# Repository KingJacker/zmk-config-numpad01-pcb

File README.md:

# NumPad01 - PCB

This Repository outlines the requirements to build a custom Keyboard with an expanded Numpad layout.

## Hardware
This Keyboard is built using the NiceNanoV2 NRF Module to leverage its Bluetooth capabilities.

It is possible to Handwire this keyboard. Altough it was deisgned with a PCB in mind.

The KiCAD files can be found in [Numpad1](/Numpad1/).
The PCB is designed to use MX Hotswap sockets.

### Key Layout
The expanded Numpad layout looks as follows.\

### Wiring
In the following Diagram it is described which pins of the NiceNanoV2 are to be soldered to the Pads on the PCB.

### Enclosure
I have deisgned a very slim Case for the PCB with just enough space for a small LiPo. You can find the OnShape Project at this [Link](https://cad.onshape.com/documents/f554f5fd452e23ddbeb69b48/w/c72bd622fd985e9e9cbd8d4f/e/263bace952513a244bd67565) or checkout the STEP files in [CAD/case](CAD/case).

###  Keycaps
This Keyboard has 21 Keys in Total.
| Amount | Type |
| ------ |----- |
| 18     | 1u   |
| 3      | 2u   |

Custom Keycaps were designed for this project, while 3D printed Keycaps may not be optimal they surely look good.

You can find the OnShape Project at this [Link](https://cad.onshape.com/documents/af3d93fce92099b4708cc048/w/839bc3040b2b1ff49a4ff1b0/e/539817a75a59442267b910fb). Since I made multiple versions I won't upload them here.

## Firmware
To utilize the full Bluetooth capabilites of the NiceNanoV2 the ZMK firmware was used. This the Keymap of this config can be changed using [Nick's Keymap Editor](https://nickcoutsos.github.io/keymap-editor/).

You can find the latest firmware on the [Releases](https://github.com/KingJacker/zmk-config-numpad01-pcb/releases/tag/release) Page.

### Flashing
If you are starting out and haven't falshed anything to the NiceNanoV2, you need to short the RESET pin to GND twice in short succession while plugged in via USB C. 

The red light will Blink and a drive will appear on your computer with the name "NiceNanoV2". Simply drag the firmware file into drive. 

That's it, the drive will disappear and the NiceNanoV2 will reboot.

Once you have flashed this firmware you can always access the bootloader to update the firmware by pressing the Layer 1 Key and Plus at the same time.

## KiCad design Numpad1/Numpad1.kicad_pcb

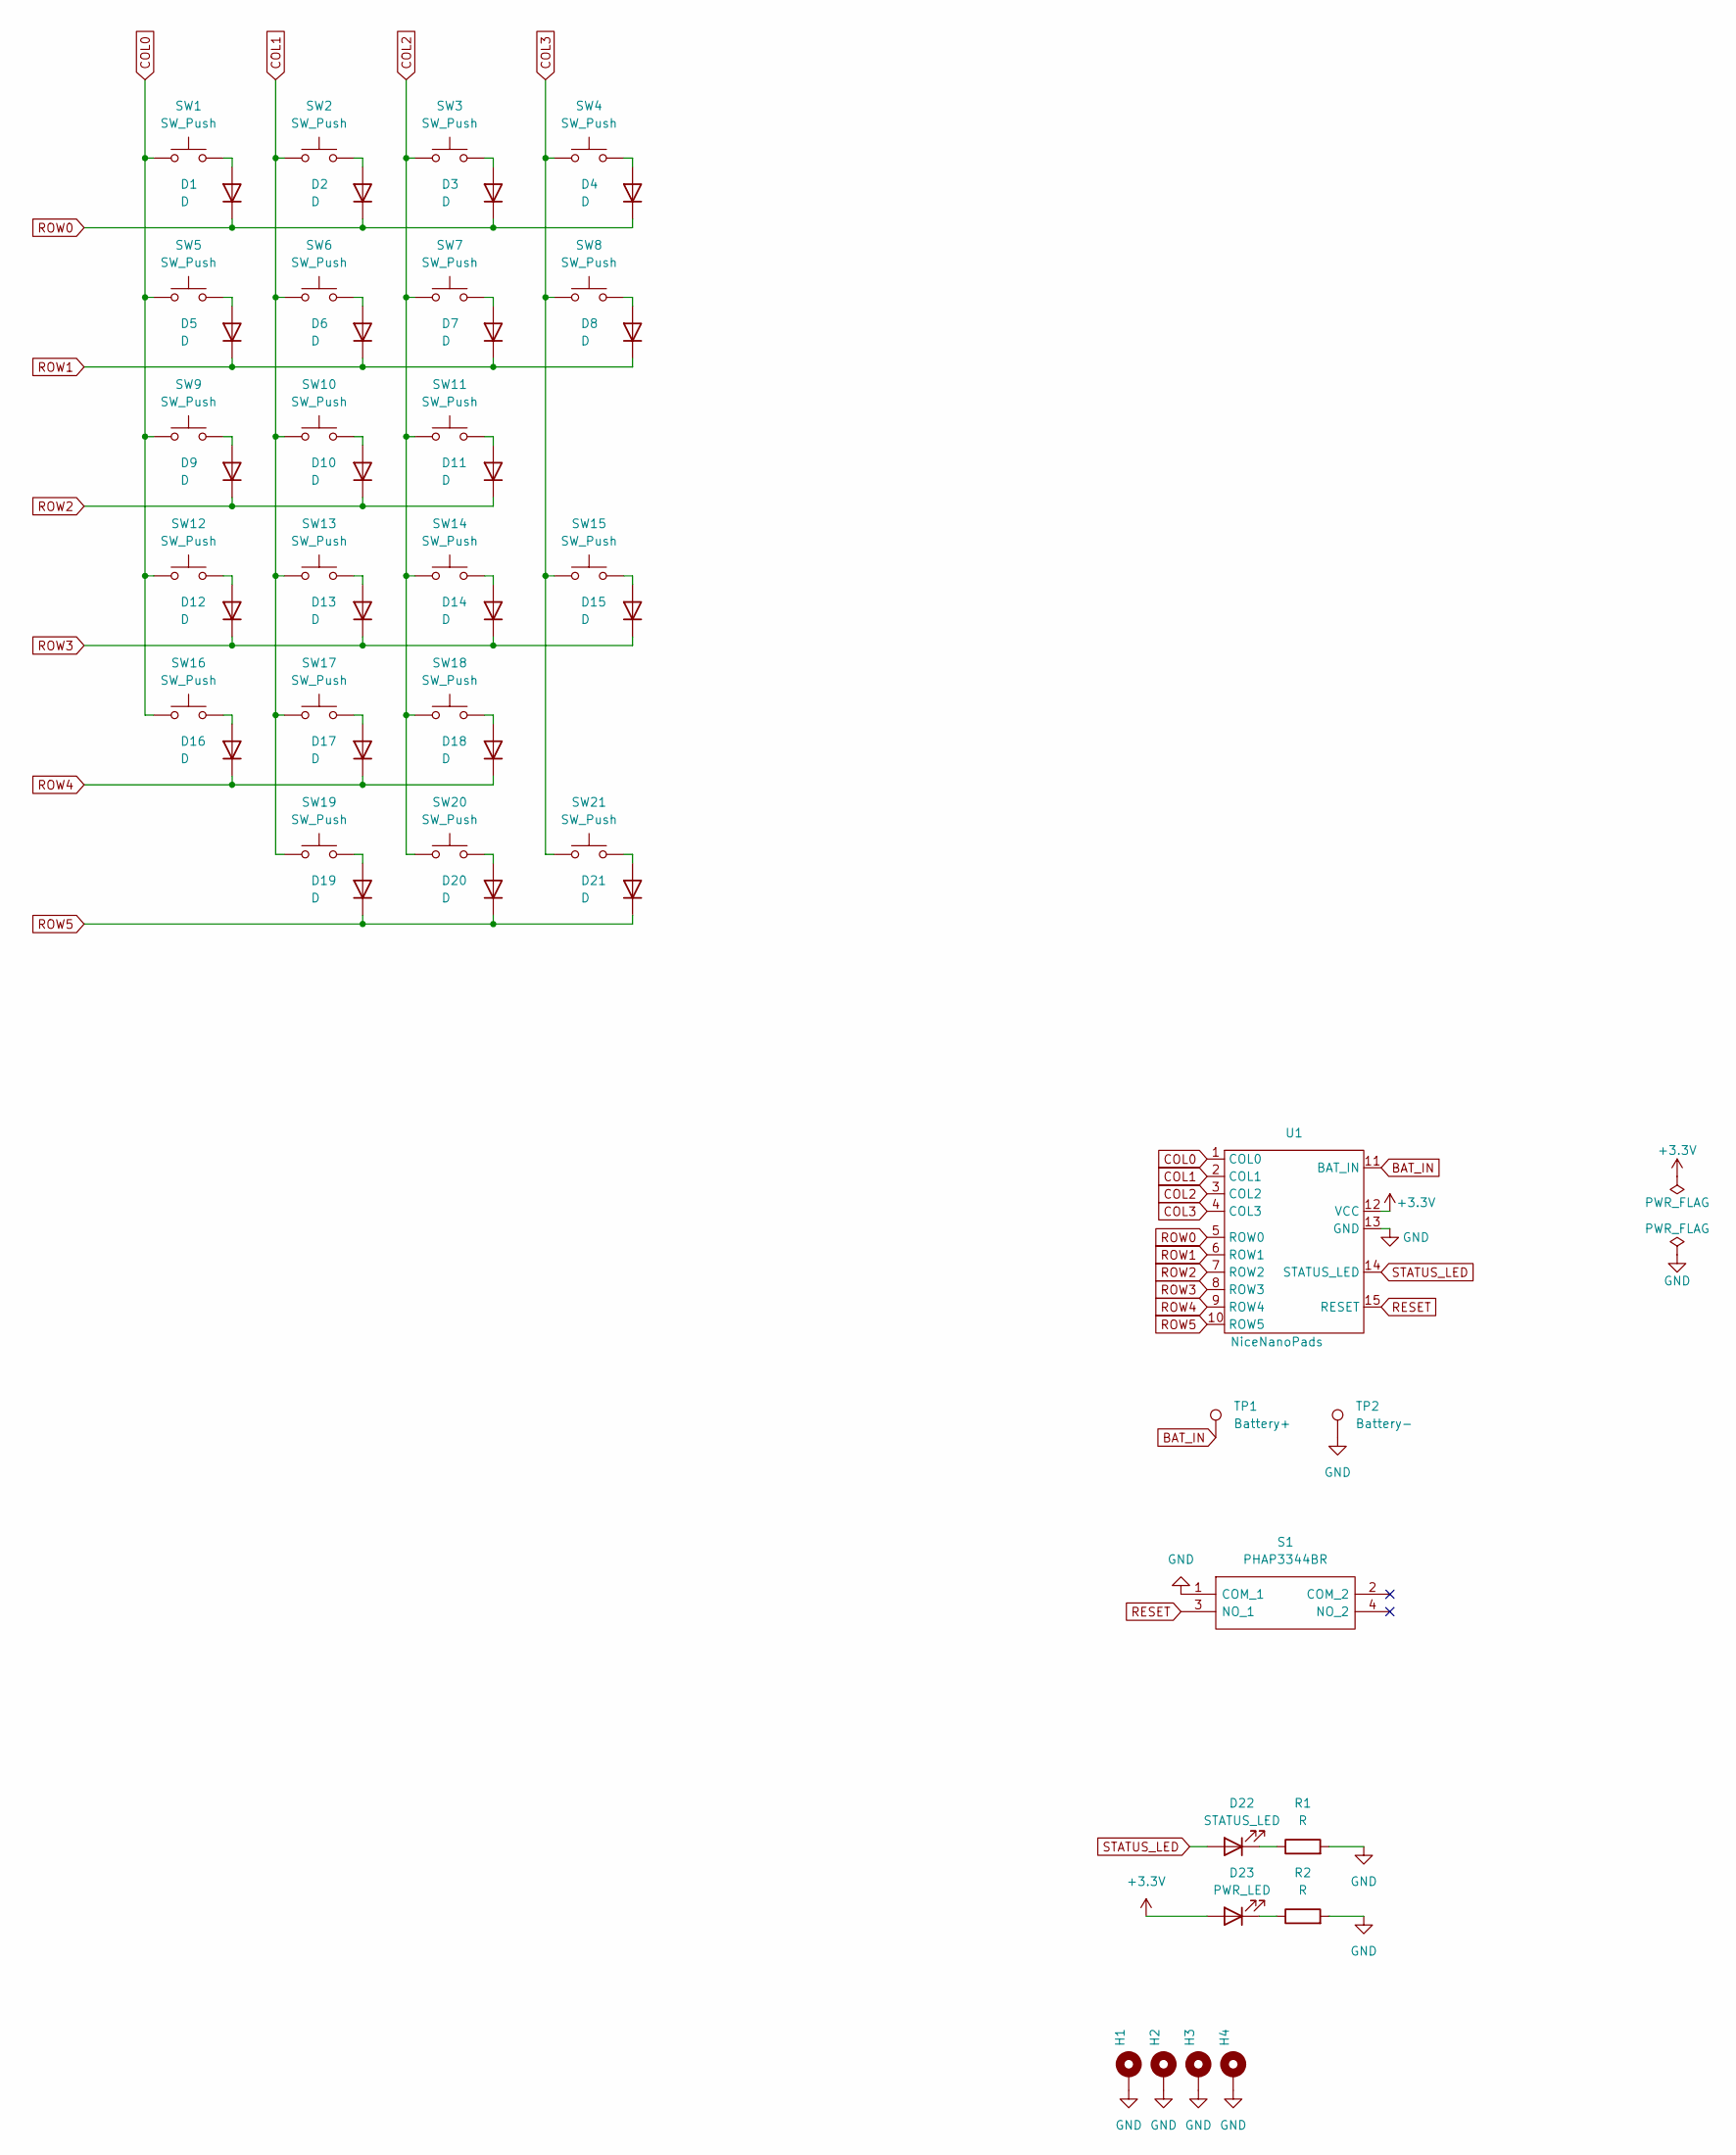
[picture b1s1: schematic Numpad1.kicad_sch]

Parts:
D1, D2, D3, D4, D5, D6, D7, D8, D9, D10, D11, D12, D13, D14, D15, D16, D17, D18, D19, D20, D21: D; D_SOD-123
D22: STATUS_LED; LED_0805_2012Metric_Pad1.15x1.40mm_HandSolder
D23: PWR_LED; LED_0805_2012Metric_Pad1.15x1.40mm_HandSolder
H1, H2, H3, H4: MountingHole_Pad; MountingHole_3.2mm_M3_DIN965_Pad
R1, R2: R; R_0805_2012Metric_Pad1.20x1.40mm_HandSolder
S1: PHAP3344BR; PTS526SM15SMTR2LFS; Mouser Part Number 642-PHAP3344BR
SW1, SW2, SW3, SW4, SW5, SW6, SW7, SW8, SW9, SW10, SW11, SW12, SW13, SW14, SW16, SW17, SW18, SW20: SW_Push; SW_Hotswap_Kailh_MX_1.00u
SW15, SW21: SW_Push; SW_Hotswap_Kailh_MX_2.00u_90deg
SW19: SW_Push; SW_Hotswap_Kailh_MX_2.00u
TP1: Battery+; TestPoint_Pad_D4.0mm
TP2: Battery-; TestPoint_Pad_D4.0mm
U1: NiceNanoPads

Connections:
+3.3V: D23.2 (A), U1.12 (VCC)
BAT_IN: TP1.1, U1.11 (BAT_IN); also elsewhere on the board
COL0: SW1.1, SW5.1, SW9.1, SW12.1, SW16.1, U1.1 (COL0)
COL1: SW2.1, SW6.1, SW10.1, SW13.1, SW17.1, SW19.1, U1.2 (COL1)
COL2: SW3.1, SW7.1, SW11.1, SW14.1, SW18.1, SW20.1, U1.3 (COL2)
COL3: SW4.1, SW8.1, SW15.1, SW21.1, U1.4 (COL3)
GND: H1.1, H2.1, H3.1, H4.1, R1.2, R2.2, S1.1 (COM_1), TP2.1, U1.13 (GND); also elsewhere on the board
unnamed: D1.2 (A), SW1.2
unnamed: D2.2 (A), SW2.2
unnamed: D3.2 (A), SW3.2
unnamed: D4.2 (A), SW4.2
unnamed: D5.2 (A), SW5.2
unnamed: D6.2 (A), SW6.2
unnamed: D7.2 (A), SW7.2
unnamed: D8.2 (A), SW8.2
unnamed: D9.2 (A), SW9.2
unnamed: D10.2 (A), SW10.2
unnamed: D11.2 (A), SW11.2
unnamed: D12.2 (A), SW12.2
unnamed: D13.2 (A), SW13.2
unnamed: D14.2 (A), SW14.2
unnamed: D15.2 (A), SW15.2
unnamed: D16.2 (A), SW16.2
unnamed: D17.2 (A), SW17.2
unnamed: D18.2 (A), SW18.2
unnamed: D19.2 (A), SW19.2
unnamed: D20.2 (A), SW20.2
unnamed: D21.2 (A), SW21.2
unnamed: D22.1 (K), R1.1
unnamed: D23.1 (K), R2.1
RESET: S1.3 (NO_1), U1.15 (RESET)
ROW0: D1.1 (K), D2.1 (K), D3.1 (K), D4.1 (K), U1.5 (ROW0)
ROW1: D5.1 (K), D6.1 (K), D7.1 (K), D8.1 (K), U1.6 (ROW1)
ROW2: D9.1 (K), D10.1 (K), D11.1 (K), U1.7 (ROW2)
ROW3: D12.1 (K), D13.1 (K), D14.1 (K), D15.1 (K), U1.8 (ROW3)
ROW4: D16.1 (K), D17.1 (K), D18.1 (K), U1.9 (ROW4)
ROW5: D19.1 (K), D20.1 (K), D21.1 (K), U1.10 (ROW5)
STATUS_LED: D22.2 (A), U1.14 (STATUS_LED)

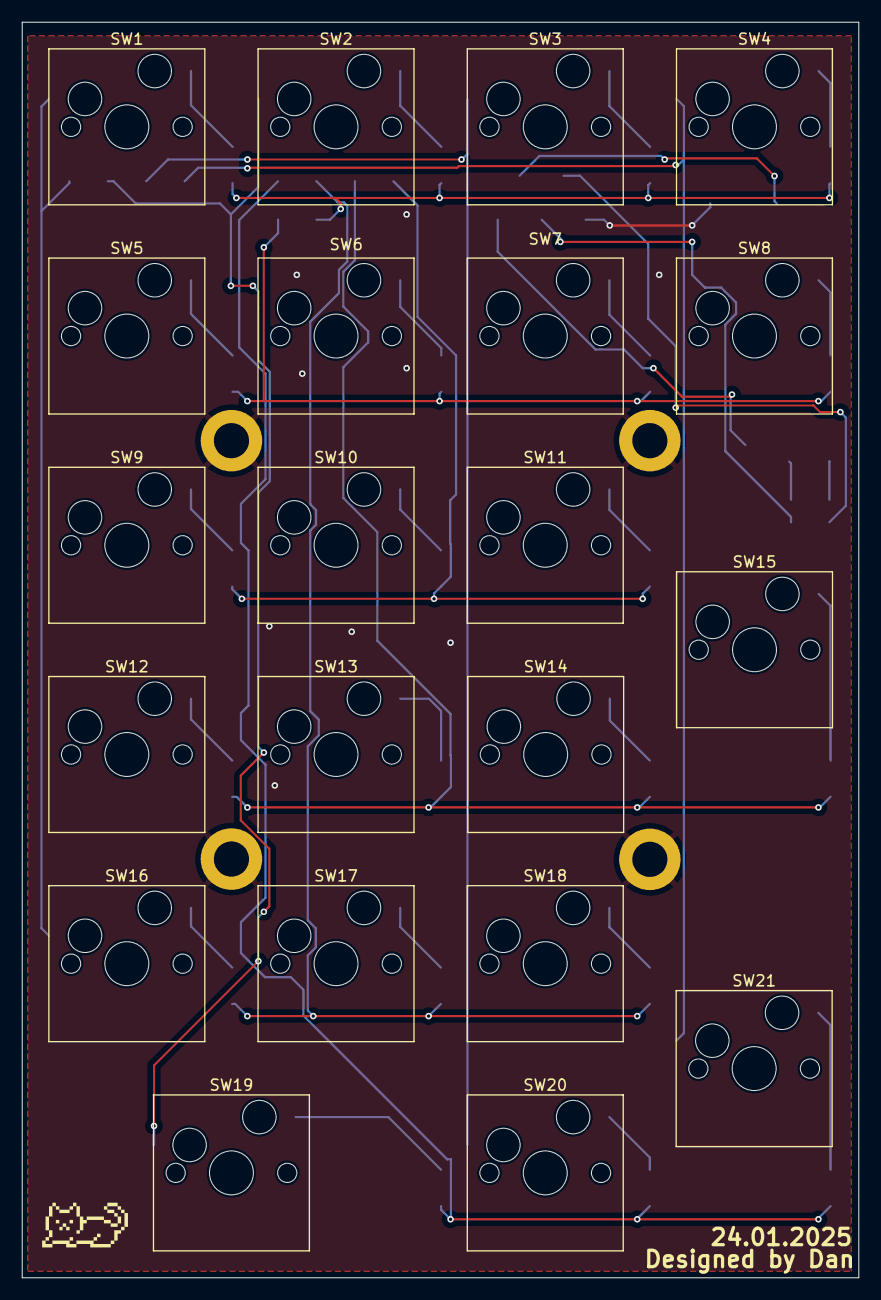
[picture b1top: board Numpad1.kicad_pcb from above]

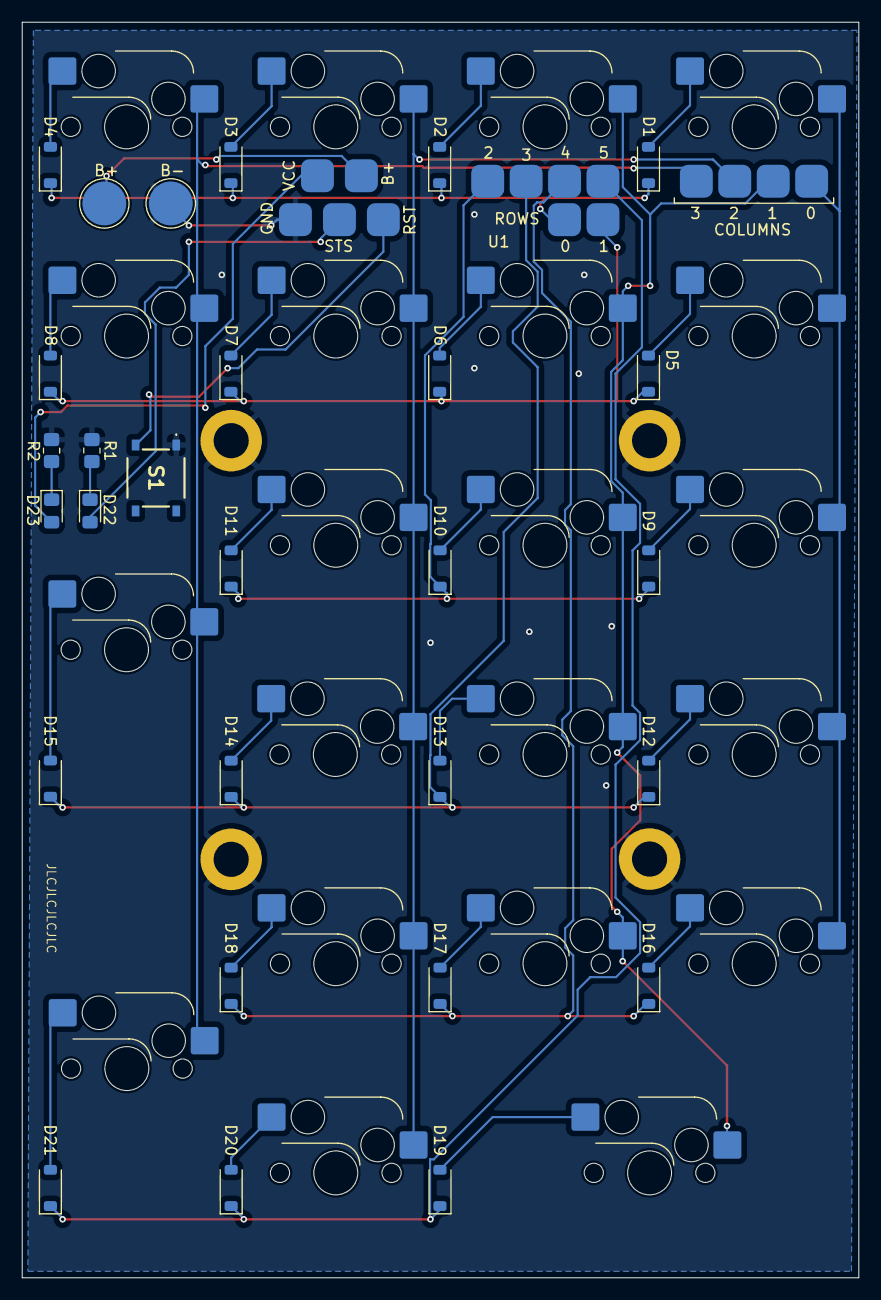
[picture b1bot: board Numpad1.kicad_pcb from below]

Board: 11 copper layers, 76.2 x 114.3 mm, 54 parts (29 on the bottom side), 38 nets.

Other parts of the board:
B+: Battery+; TestPoint_Pad_D4.0mm
B-: Battery-; TestPoint_Pad_D4.0mm

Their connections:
BAT_IN: B+.1; also elsewhere on the board
GND: B-.1; also elsewhere on the board

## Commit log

2025-02-10 Initial User Config.
2025-02-10 fixed config
2025-02-10 fixed config 01
2025-02-10 fixed difference in wiring for 2u switches
2025-02-10 Alpha Version
2025-02-10 Alpha Version 01
2025-02-10 Alpha Version 02
2025-02-23 MediaPad01-firmware_00
2025-02-23 mediapad01-firmware_01
2025-02-23 mediapad01-firmware_02
2025-02-23 mediapad01-firmware_03
2025-02-24 added encoder 0
2025-02-24 encoder 1
2025-02-24 encoder 2
2025-02-24 encoder 4
2025-02-24 encoder 5
2025-02-24 encoder 6
2025-02-25 encoder 7
2025-02-25 encoder 8
2025-02-25 encoder 9
2025-02-26 encoder 10
2025-02-26 encoder 11
2025-02-26 encoder 12
2025-02-26 encoder 13
2025-02-26 encoder 13.1
2025-02-26 debug 0
2025-02-26 encoder 14
2025-02-26 disable logging, encoder final
2025-02-26 fast forward/ rewind
2025-02-26 fast forward /backward 1
2025-02-26 Fastforward, rewind & nice overview of keymap
2025-02-26 rewind fastforward not working so reverting to left and right arrowkeys
2025-06-26 enable spi, setup for key configurator
2025-06-26 added display name to fn layer
2025-06-26 moved to correct folder
2025-06-26 correct key placement
2025-06-26 readme, imgs, kicad files, stepfile
